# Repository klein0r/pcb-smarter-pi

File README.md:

# Smarter Pi PCB

[Gerber-Files](https://github.com/klein0r/pcb-smarter-pi/releases)

## Preview

## Features

- 1-Wire Interface (GPIO4)
- Reed sensor Support (GPIO22)
- RJ10 for serial interface (RX / TX)
- 3x SMD LED
- 3x Buttons (SMD or external terminal block)

## Parts

- J1: MPE 094-2-040 (20x2 connector)
- J2: MEBP4-4
- J3, J5: PHC 1725672 - MPT 0,5/ 4-2,54
- J4: PHC 1725669 - MPT 0,5/ 3-2,54
- R1: Resistor DIN0207 2.2k
- R2: Resistor DIN0207 4.7k
- R3, R4, R5: Resistor SMD 0805 330
- R6, R7, R8: Resistor SMD 0805 10k
- D1, D2, D3: LED SMD 0805
- SW1, SW2, SW3: Push Button (3.81)
- U1: DS18B20

## License

The MIT License (MIT)

Copyright (c) 2026 Matthias Kleine <info@haus-automatisierung.com>

Permission is hereby granted, free of charge, to any person obtaining a copy
of this software and associated documentation files (the "Software"), to deal
in the Software without restriction, including without limitation the rights
to use, copy, modify, merge, publish, distribute, sublicense, and/or sell
copies of the Software, and to permit persons to whom the Software is
furnished to do so, subject to the following conditions:

The above copyright notice and this permission notice shall be included in
all copies or substantial portions of the Software.

THE SOFTWARE IS PROVIDED "AS IS", WITHOUT WARRANTY OF ANY KIND, EXPRESS OR
IMPLIED, INCLUDING BUT NOT LIMITED TO THE WARRANTIES OF MERCHANTABILITY,
FITNESS FOR A PARTICULAR PURPOSE AND NONINFRINGEMENT. IN NO EVENT SHALL THE
AUTHORS OR COPYRIGHT HOLDERS BE LIABLE FOR ANY CLAIM, DAMAGES OR OTHER
LIABILITY, WHETHER IN AN ACTION OF CONTRACT, TORT OR OTHERWISE, ARISING FROM,
OUT OF OR IN CONNECTION WITH THE SOFTWARE OR THE USE OR OTHER DEALINGS IN
THE SOFTWARE.

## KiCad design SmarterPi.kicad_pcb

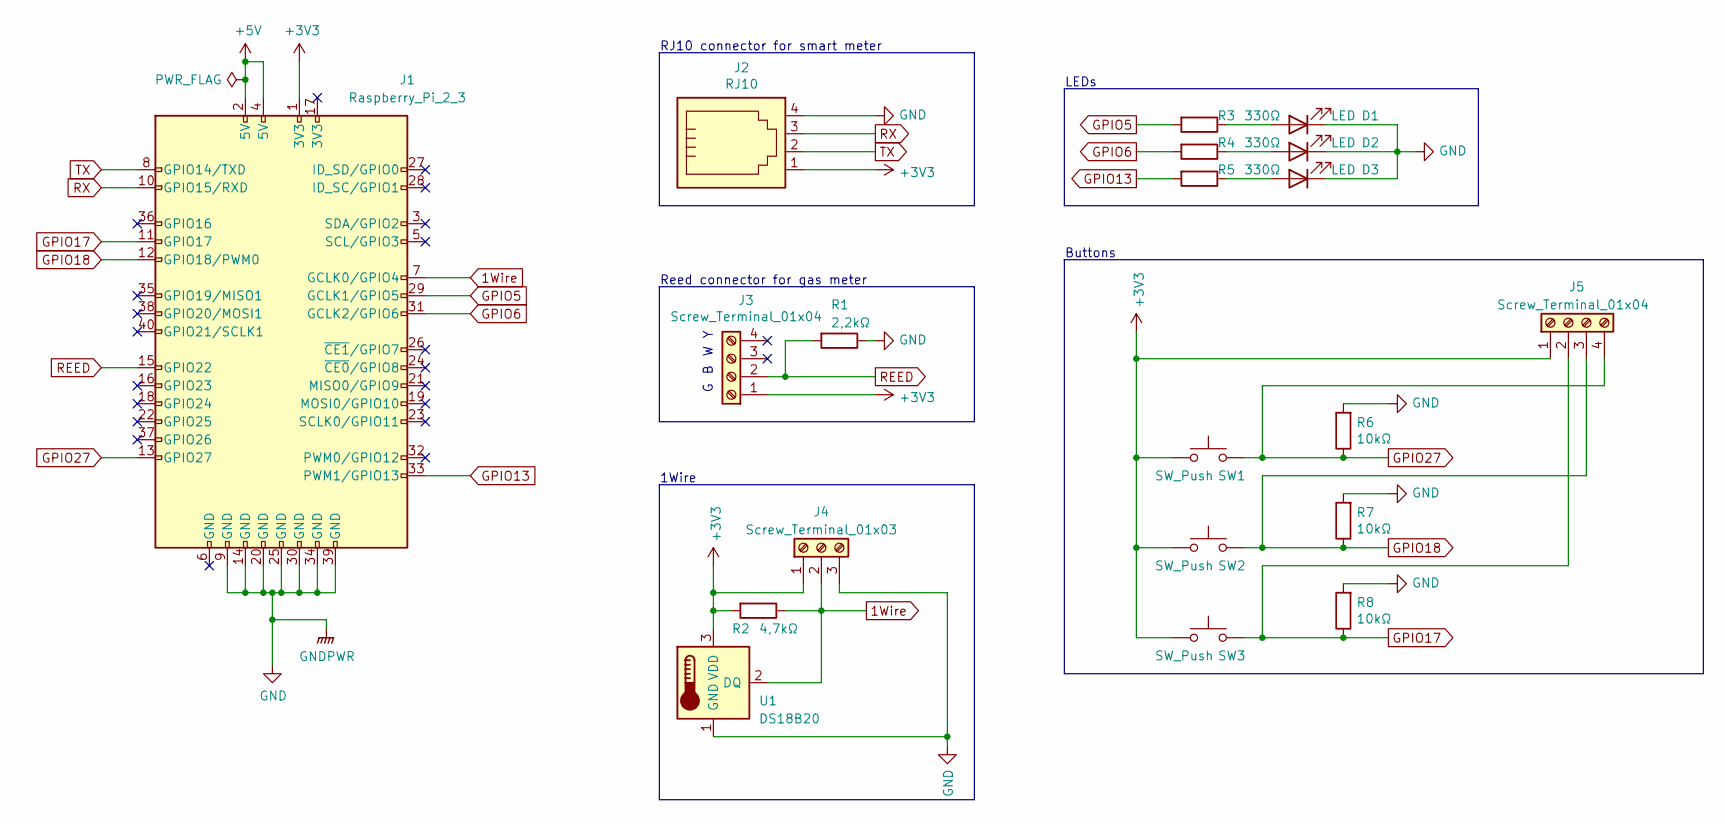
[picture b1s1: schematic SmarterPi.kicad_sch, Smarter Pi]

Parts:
D1, D2, D3: LED; LED_0805_2012Metric_Pad1.15x1.40mm_HandSolder
J1: Raspberry_Pi_2_3; PinSocket_2x20_P2.54mm_Vertical
J2: RJ10; MEBP_44S
J3, J5: Screw_Terminal_01x04; TerminalBlock_Phoenix_MPT-0,5-4-2.54_1x04_P2.54mm_Horizontal
J4: Screw_Terminal_01x03; TerminalBlock_Phoenix_MPT-0,5-3-2.54_1x03_P2.54mm_Horizontal
R1: 2,2kΩ; R_Axial_DIN0207_L6.3mm_D2.5mm_P10.16mm_Horizontal
R2: 4,7kΩ; R_Axial_DIN0207_L6.3mm_D2.5mm_P10.16mm_Horizontal
R3, R4, R5: 330Ω; R_0805_2012Metric_Pad1.20x1.40mm_HandSolder
R6, R7, R8: 10kΩ; R_0805_2012Metric_Pad1.20x1.40mm_HandSolder
SW1, SW2, SW3: SW_Push; SW_SPST_CK_RS282G05A3
U1: DS18B20; TO-92_Inline

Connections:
1Wire: J1.7 (GCLK0/GPIO4), J4.2, R2.1, U1.2 (DQ)
+3V3: J1.1 (3V3), J2.1, J3.1, J4.1, J5.1, R2.2, SW1.1, SW2.1, SW3.1, U1.3 (VDD)
+5V: J1.2 (5V), J1.4 (5V)
GND: D1.1 (K), D2.1 (K), D3.1 (K), J1.9 (GND), J1.14 (GND), J1.20 (GND), J1.25 (GND), J1.30 (GND), J1.34 (GND), J1.39 (GND), J2.4, J4.3, R1.1, R6.2, R7.2, R8.2, U1.1 (GND)
GPIO5: J1.29 (GCLK1/GPIO5), R3.2
GPIO6: J1.31 (GCLK2/GPIO6), R4.2
GPIO13: J1.33 (PWM1/GPIO13), R5.2
GPIO17: J1.11 (GPIO17), J5.2, R8.1, SW3.2
GPIO18: J1.12 (GPIO18/PWM0), J5.3, R7.1, SW2.2
GPIO27: J1.13 (GPIO27), J5.4, R6.1, SW1.2
unnamed: D1.2 (A), R3.1
unnamed: D2.2 (A), R4.1
unnamed: D3.2 (A), R5.1
REED: J1.15 (GPIO22), J3.2, R1.2
RX: J1.10 (GPIO15/RXD), J2.3
TX: J1.8 (GPIO14/TXD), J2.2

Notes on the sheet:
RJ10 connector for smart meter
1Wire
Reed connector for gas meter
Buttons
LEDs

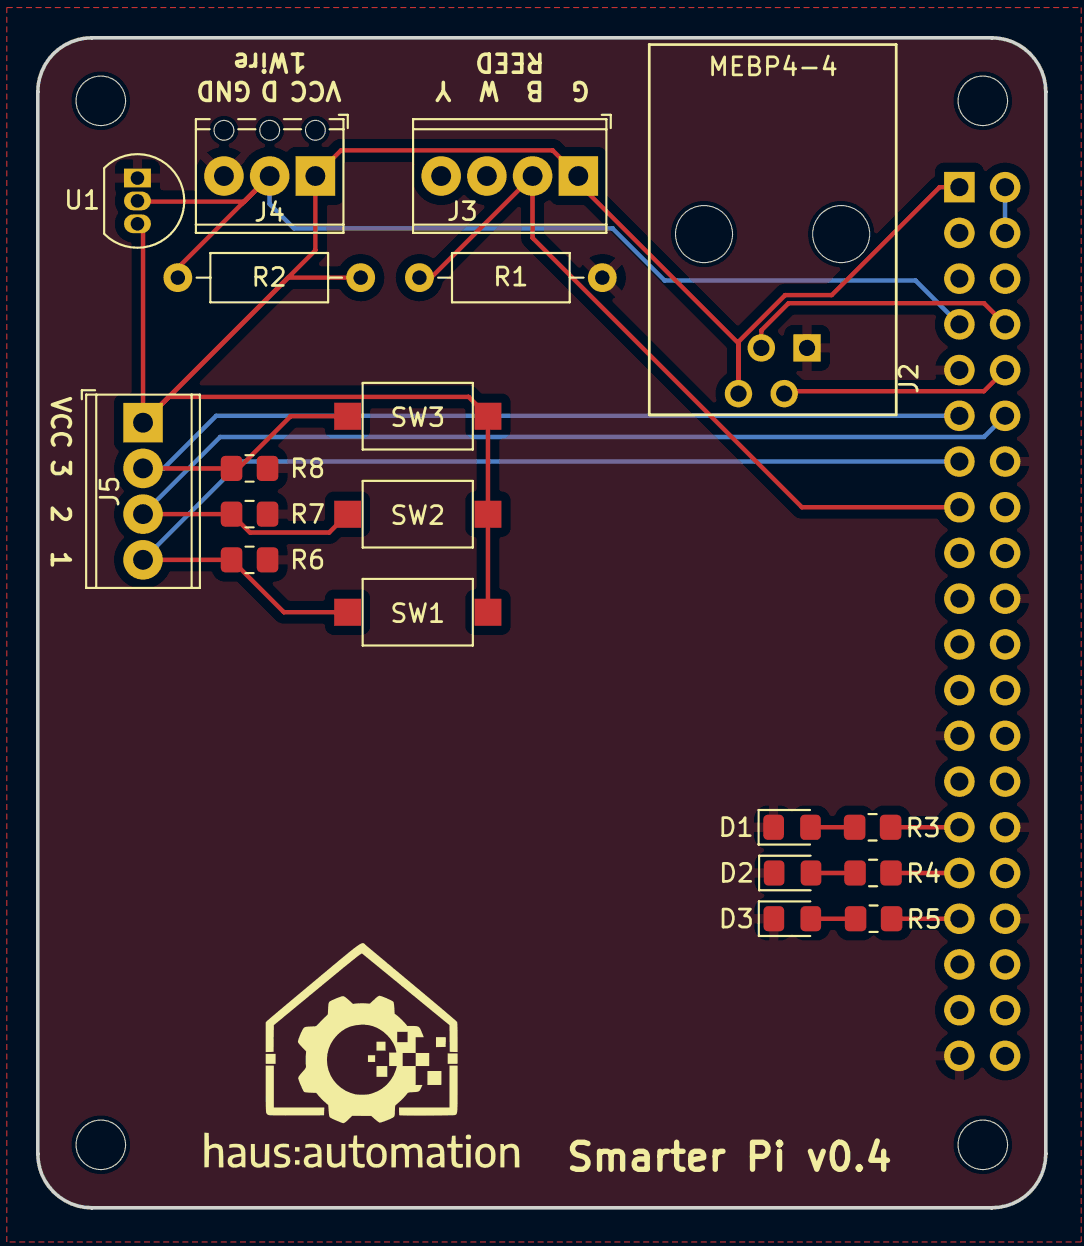
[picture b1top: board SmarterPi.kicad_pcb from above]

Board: 2 copper layers, 56.0 x 65.0 mm, 24 parts (1 on the bottom side), 16 nets.

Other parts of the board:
H1, H2, H5, H6: MountingHole; MountingHole_2.75mm_NoPad

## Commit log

2021-02-02 RJ10 Adapter for serial
2021-02-03 Reed
2021-02-03 1Wire
2021-02-18 Readme, License, Preview
2021-02-18 Added LEDs
2021-02-19 Added 3 push buttons
2021-02-19 Readme update
2021-02-19 Minor fixes
2021-10-13 Preview Photo
2021-10-21 Smaller terminal block for buttons
2021-10-21 Added DS18B20
2022-01-30 Update LICENSE
2022-01-30 Updated to KiCad 6
2024-03-15 v0.3
2024-05-06 v0.4
2026-01-28 Year 2026
